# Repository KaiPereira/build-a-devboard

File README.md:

# Let's Design an RP2040 Devboard!

Today, we're going to be designing our own dev board, using one of the most popular and beginner friendly SoC's, the RP2040. This guide doesn't serve as just a tutorial, but also as an opportunity to learn what everything on the PCB fundamentally does, and what every single component on your PCB is actually for!

All the source files for this tutorial can be [found here](https://github.com/KaiPereira/build-a-devboard), so if you need any help, feel free to resort to the repository!

Now let's start off with the basic question, what's an SoC! An SoC or system on chip, basically has all the basic components like SRAM, processors, USB controllers, and other peripherals you'll break out onto your board. The RP2040 is a good SoC to start with, because the datasheets are simple, it's low-cost, has good on-chip memory and is really flexible with plenty of IO's.

Now let's get right into it, we'll be using KiCad for this tutorial, and I would suggest completing the hackpad tutorial and maybe a keyboard before trying to make your own devboard, not because you won't be able to make it, but you'll understand how it works a bit better.

So create a new KiCad project by going:
`File -> new project, and choosing your name/folder for the project`

After that, double click your schematic to start working on your PCB. PCB's essentially have 2 main parts, the schematic, and the actual PCB. 

The schematic is basically a wiring diagram, that shows how everything will connect, but isn't like exactly where the components are placed or how thick your traces are, it's solely to show how everything is wired, not where.

*This is how are schematic will look when done the tutorial*

The PCB editor is where you'll place down all your components and route everything for when you get it actually manufactured.

## Starting the schematic

So enter in your schematic, and then tap "a", this will open up the symbol library, which is the place where you can find component blocks that you'll wire together to form the schematic for your project. Search for the RP2040, and just place it down in the center of your schematic.

You'll notice the symbol and actual component are 2 different things if you look at the first screenshot. The symbol just tells you all the pins on the component, and how they'll be wired to what. The actual component has the physical pads where traces will actually connect to on your PCB!

Our entire schematic will consist of 5 main elements: power, flash storage, the crystal oscillator, I/O (input/outputs), and your SoC, the RP2040! The Raspberry Pi datasheet explains how all of this will pretty much be wired, and I'm kind of just here to explain exactly how it all works too.

So first let's talk about power and some schematic good practices!

You'll notice that the RP2040 has capacitors, these are called decoupling capacitors. These capacitors are used for 2 main things, filtering out power supply noise and giving a local power supply if components need it at short notice. You can think of it like a stream of water, without the capacitors it can be jittery and unpredictable, but with the capacitors, the stream smooths out, making your PCB function more reliable.

You usually want to put one 0.1uF (or 100nF, the F stands for Farads) decoupling capacitor per power pin, but it's fine to deviate a bit from that, but that's the most optimal way of doing it and what we're going to do.

We're also going to put a 1uF decoupling capacitor on each power line. You'll notice that the RP2040 has a +1V1 (1.1V) and a +3V3 (3.3V) line, we want to put a 1uF decoupling capacitor per line, to act as a larger reservoir and to smoothen out *larger* ripples that could occur. With the RP2040, these 1uF capacitors are mostly to help provide a stable 1.1V supply. With this combination, we'll filter out nearly all the noise and have a smooth functioning PCB.

So go back into your schematic and then tap on the "Draw Wires" icon to connect the VREF_VOUT and DVDD, and then separately connect the IO_VDD, USB_VDD, ADC_AVDD and VREG_IN, because these pins have different voltages.

**Now before we go further, remember that all power labels face UPWARDS, and all ground labels face DOWNWARDS, this isn't necessary for the schematic to work, but it's good schematic practices that you should always follow**

Then tap "p" to open up the POWER symbol library (you can also tap a, but searching in p will be faster because there's less symbols), and search for "1V1" and "3V3" and place the 1.1V on the VREG_VOUT and DVDD, and 3.3V on the IOVDD and those other pins.

**Now schematic good practices is to always put at least a small wire between symbols like this for clarity.** 

Now that we have our power symbols in, we're going to add the decoupling. You could technically wire them like the screenshot I showed before, but I prefer to separate them because you use less wire which I find looks cleaner, but it's up to personal preference, and readability.

You'll also notice that the symbol contains less pins than the symbol the RP2040 datasheet has, this is because symbols in KiCad tend to not repeat the same pins, so they just merge like all the same VDD pins into one.

But using the RP2040 datasheet as reference, we know that there's 8 IO VDD pins, so eight 0.1uF decoupling, and one 1uF cap because we're wiring the entire 3.3V line and need to smooth out the larger ripples. So let's just place all those in!

Again type "a" and search for "c" (the shorthand for capacitor). Make sure to double tap the capacitors to add a value, and make eight of them 0.1uF, and one of them 1uF.

These are the decoupling capacitors for the 3.3V line, now we need to do the caps for the 1.1V line. There's 2 VDD pins, so two, 0.1uF caps, and we need one for the line too, so a 1uF cap aswell:

Now we have all of our power decoupling. We also need to connect GND to the SoC, this is pretty self-explanatory, but it allows power to actually flow properly in our PCB.

## Working on USB-C

We have our power decoupling, but we don't actually have a power source yet or a way to program our devboard yet, so let's do that now. I'm going to be using USB-C because it's standard and fast!

So tap "a", type in whatever receptacle you want, and add it in. Make sure you pick "receptacle" and not plug because a plug would plug into your laptop instead of having a cable plug into it.

Now let's explain each of these pins:
- SHIELD/GND will both go to ground, shield is conductive material wrapped around the data pins on the receptacle, and this just improves EMI by grounding it.
- D+/D- are the data pins, these transfer data to/from the USB-C receptacle. You'll want to connect the D-'s and D+'s together so that they both transfer data.
- CC1 and CC2 basically tell the receptacle to allow power to go through to power the board. These by standard (the datasheet tells you) are pulled down (go to GND) through 5.1K resistors.
- VBUS is the 5V input, this will need to be stepped down to 3.3V to power our MCU (microcontroller)

Now that we know what everything does, let's wire it up. Shield/GND go to GND:

D+ and D- are attached to their relative pair, and then will go into the MCU, but for now, we'll just have a global label going out of them. Global labels are basically like little teleporters, that allow you to say that something is wiring, without manually putting a wire between them. 

Technically global labels are meant to be used between different schematic sheets and net labels would be the correct thing to use here, but I find global labels are cleaner if you only have one schematic for your PCB.

To do this, tap global label in the right hand toolbar, type in the name for your label (USB_D+ and USB_D-), and add them to the pins:

Next, pulldown the CC pins through a 5.1K resistor to GND to enable power to go through the USB-C receptacle. Open up the symbol library, and then type "r" the shorthand for resistors, and then place it down and edit the value to be 5.1K:

**Remember to follow proper schematic good practices, and to have clearly visible values, and labels for your components**. Feel free to edit the text of stuff to make your schematic cleaner, just don't make stuff *too* small.

Now we just need to wire in the input voltage, but the thing is, the voltage of USB-C is 5V, while the voltage that the RP2040 uses as input, needs to be 3.3V so you don't cook it. To achieve this, we'll use what's called an LDO, or a Low-Dropout Regulator to take the voltage down.

Specifically, we'll be using the **NCP1117**, a classic and reliable *fixed* voltage regulator **(I actually switch this regulator out later for the MCP1700, 3.3V, because it's really big on our PCB)**. A fixed voltage regulator is handy here, because we only need to go down to 3.3V instead of like 1.5V per say or something random, and it uses less components. We'll also be using the SOT-223 footprint (or package is the common term) because it's small and we don't really have any thermal issues with a devboard.

So add in the **NCP1117-3.3_SOT223** symbol, wire GND and attach VBUS to the VI (voltage input) of the LDO.

Remember to always keep your schematic clean and feel free to use up quite a bit of space. Now like the decoupling capacitors on our RP2040, we need capacitors on the LDO. But we don't need fine decoupling capacitors for precise input lines into an MCU, and instead we need **bulk** capacitors, to handle the large voltage ripples when moving a voltage down.

So we need to place two, 10uF capacitors on each side of the LDO, for input/output, so add them into your schematic:

Next, we want to add our power labels to the LDO, we'll put a VBUS label **before** the LDO/Bulk cap, and a +3V3 label to the VO (voltage out) of the LDO. We might use 5V to power some other devices so we'll want to provide a power line for that too:

Now to finish off the USB-C wiring, we need to make sure the MCU receives the data lines. It's standard to have these going through 27 ohm resistors into the MCU to prevent distortions of the signals at high speeds, these are called *termination resistors*.

So wire the USB D+ and D- pairs into the MCU USB_DP and USB_DM (the P is for + and the M is for -) through 27 ohm resistors:

Now USB D+ and D- are actually what's called "bidirectional", this means that they work both ways. You don't actually need to specify this, but good schematic practices is to make sure your global labels reflect that. Currently they're just set as "inputs" because the triangle is facing inwards, so double click on all the D+ and D- labels and set them to bidirectional:

## The crystal oscillator

Now to make our USB and other peripherals actually work properly, we need to have what's called a crystal oscillator. This is a little piezoelectric quartz crystal that vibrates very precisely, and then it's amplified and fed into the MCU to act as a clock signal that controls the digital peripherals.

For example, you definitely want a crystal oscillator if you're using USB-C, because the data needs to come in at specific times, so it makes sure no data is incorrectly received. Because the clock is such a precise component, you want to wire it really carefully. That means it should be as close to the MCU as possible on the PCB (schematic doesn't matter, it's just a reference), and it needs really small capacitors, to smooth out the signals.

First add the global labels to the MCU XIN and XOUT, just called their relative name. XOUT is the output from the crystal so an input to the MCU, and XIN is an output from the MCU to help the crystal oscillate properly:

Remember to accurately represent your global label direction, but just keep in mind it doesn't actually change your schematic, it's only for whoever is reading it!

Based off the RP2040 datasheet, we're going to be using a 12 MHz crystal with two, 15pF (I switch these later to 33pF because we use a different crystal than the Pi Pico) decoupling capacitors. **Make sure to use the crystal footprint with 4 pins and 1 and 3, as the input/output pins so pay attention to the symbol I use**:

Pins 2, and 4 just go to GND, pins 1 and 3 need a 15pF cap in series, and XOUT will have a 1K resistor. This resistor is called a damping resistor and it prevents the crystal from being damaged and ensures good signal integrity:

Remember all your schematic good practices and make sure everything looks clean.

We haven't actually seen these types of caps yet, these are called external load capacitors, and they're placed in series with the crystal I/O's, these basically just ensure that the crystal resonates at it's proper frequency, I'd suggest researching a bit more if you're interested!

## Flash storage

Now lot's of SoC's include flash storage, but the RP2040 actually doesn't, so we need to add on our own flash storage! You can think of flash storage as like a faster version of an HDD, with less power consumption, more reliability but is usually a bit more expensive.

Sadly, the RP2040 only supports up to 16mb of memory, so we'll just use a quad SPI flash memory IC (integrated circuit, those little chips on a board) like the **W25Q128JVS** used in the datasheet.

Now before we actually add it to our schematic, let's talk about what SPI is. If you continue to build PCB's, you'll see this communication interface very often, it's basically just a standardized way of transferring data. The signal comes out of the master, and then goes into slave devices. The master is our MCU in this case, and the slave, is our flash memory.

It has 4 major pins you need to understand:
- MOSI - Master output, slave input
- MISO - Master input, slave output
- SCLK - Clock signal (remember that oscillator we added to our board, this will basically do that for other devices)
- SS/CS - Slave select, let's you choose what device you're communicating with

So you usually need to have all 4 of those, and then you can add SS pins as you wish if you want to communicate with more and more devices.

**But we're actually using quad SPI in this case.** 

Quad SPI uses the same CLK and CS pin, but has 4 IO pins, so it can transfer data, 4x as fast as SPI, which is ideal for flash memory, but it does take up more pins, so that's why it's not always used. 

Now you can't just attach SPI to any GPIO, you have to use what's called a hardware controller, which you can imagine, is like a little block on the RP2040 SoC that is specifically meant for SPI. There are 2 SPI controllers on the RP2040, so we're going to use them for our flash memory. You can also technically do SPI via software, but it just makes way more sense to use the actual controller provided.

So add a global label to the QSPI pins with their relative name, IO's are bidirectional, and CLK and CS/SS are inputs to the slave (the flash memory) or outputs from the MCU.

Next, add in our flash memory IC (chip), **W25Q128JVS**, and wire up all the QSPI pins, and put GND to GND, and VCC to 3.3V:

Next, we need to add our 100nF/0.1uF decoupling capacitor to our VCC line to filter high-frequency noise. And then, we're going to add a button to the CS line, so that we can enter what's called BOOTSEL mode.

Based off of the RP2040 datasheet, if the QSPI SS pin, see's a 0 or GND when it's booting up, it'll go into BOOTSEL, where it will appear as a USB device on our computer so that we can copy code onto it to set it up.

Now there's 2 resistors you're probably wondering about here, the pullup to 3.3V, and the one in series with the button.

The pullup to 3.3V is important, because usually the QSPI pin will show up as 3.3V to the flash memory, but during bootup, you can't guarantee that it will, because the pin isn't active, so you might have some weird thing that happens with your board. The 10K resistor is just standard that the RP2040 datasheet wants us to use (and is also pretty commonly used to filter noise and stuff).

The 1K resistor in series limits the amount of current that can flow in this part of the circuit to prevent damage to the CS pin.

And just like that, we have our button and decoupling in, and our flash memory is completed!

## Breaking out I/O Headers

Now we have all the components for our board to actually work, so we just need to breakout all the GPIO's on the RP2040, onto header pins so that we can use them in our circuit and whatnot!

But before we do this, let's just make sure we attach TESTEN to GND on the RP2040, this pin is just meant for factories to make sure that the RP2040 SoC actually works before sending them out.

Next, we'll label all the other pins we haven't broken out (all the GPIO's, SWCLK and SWD), with their relative name on the RP2040. These are all bidirectional pins except the SWCLK pin, which is a clock output from the SoC:

*I actually labelled mine the wrong direction for the rest of this tutorial, but it's purely cosmetic and won't actually impact my PCB, this is how it should actually look, don't mind the GPIO labels, I took this screenshot after being done the PCB:*

Next, we're going to add the actual header pin symbols into our schematic. You can technically do this whoever you want, but I'm going to adhere to the raspberry Pi Pico pinout:

So add in a two, 1x20 header pin symbols, and one 1x3 header pin symbol, I just used generic symbols, but you could use pin header symbols if you want, it's just up to preference:

Usually you don't want to make your symbol layout look exactly like your PCB, but I think it makes it more obvious so that we don't mess up our pinout!

Next, we'll just add in all the pins, and we'll just leave out the ones we don't know yet like VSYS, 3V3_EN and ADC_VREF, I'll explain those after:

Now the Pi Pico can actually be powered by a battery, but we're not implementing a battery (if you want to, check out the Pi Pico datasheet), so there's a diode on the VBUS power line, so they have a VSYS line after the diode and a VBUS line before it, but because we don't need a diode, we don't need VSYS.

We also don't need 3V3_EN, and then ADC_VREF is kind of just another thing to give a reference voltage to ADC, but it isn't really necessary, and we're just making a simple devboard so we won't use it.

Because we have these free pins, and also some GPIO's still left, let's just fill these pins with some GPIO's. I'm going to move the ADC pins up, and then fill the other pins with GPIO's. I also want to use GPIO29 which is an ADC pin and replace GPIO25 with that just so we get the added ADC pin:

Because of this, you'll want to just no-connect GPIO25 on the MCU, just to tell KiCad and others that we're not using that pin:

If you want to add battery support, you can do so yourself, but I'm keeping to a minimum framework. And just like that, we have all of our header pins in!
## Finishing up the schematic

Now that we have our I/O headers in, we're actually finished with all the symbols in our schematic, this is how your schematic should look:

Now to organize our schematic, even more, let's separate our design into different blocks using the text boxes in the schematic editor. When doing this, you usually want to place your component blocks by flow of your PCB. So if you could image, power flows in through the USB, so we'll put that in the corner, the MCU should be center because it's the fundamental of the PCB, and then the other stuff can just be organized around:

You don't have to do this, but I feel like it keeps everything nice and clean!

Next, run ERC to just make sure you don't have any unconnected or weird stuff happening in your schematic. The only error you might get is **Input Power pin not driven by any Output Power pins**. You can just ignore this error, it's basically just the fact that we're labelling our power as bidirectional, and with no input/output, but we know that the MCU takes in 3.3V and that the USB-C outputs 3.3V, so we're totally fine to ignore it.

## Footprint time!

Now that we've finished out schematic, we need to start working on the actual PCB. The first thing you need to do for the actual PCB, is to add in all the footprints for your components.

A footprint on a PCB basically just defines it's pads, outline, etc, that your component needs in order to be solder able on a PCB. So just tap on the **assign footprints** tab in the top toolbar to open up the footprints tab:

Now before we add in our footprints, let's talk about standard imperial sizes of SMD components, and SMD vs THT components.

So if you don't know, there's SMD components, which are surface mount, which means that the components are attached to the surface of the PCB like caps, and then there's THT components, which are soldered *through* the board, these are things like the headers.

For SMD footprints, you'll want to understand what the imperial sizes are:
- 0402 are the smallest footprint we'll have on our PCB, these are tiny footprints and anything smaller than this becomes too small to easily solder, these are good for low current applications, and are fine for our fine signal decoupling.
- 0603 footprints are a bit larger than 0402, and are better for slightly higher current and will maintain better physical stability for the larger decoupling needed for 10uF caps and such.
- 0805 footprints are pretty large and are really just needed in higher current applications, we won't be using any of these because we don't have any crazy large caps/components

So all of our 0.1uF/1uF/resistors will be 0402, and then the 10uF caps will be 0603, so just filter in the search bar for 0402/0603, and choose the resistor/capacitor footprint for the relative component:

Now these other components need to usually be found on LCSC and then you go into the datasheet to find the footprint, and then add it in, but I'm decently experienced and know what footprints to use already, so you can just copy what ones I'm using or [find your own](https://jlcpcb.com/parts) if you want and add them in:

These are my thought process behind the other components, JLCPCB has what's called basic and extended parts, and extended parts cost $3 each to add to a PCB because they have to be loaded into the assembly machines, this will be important here:
- **USB_C_Receptacle_HRO_TYPE-C-31-M-12**: JLCPCB doesn't have any basic part USB-C receptacles, so I just chose this one I kind of like from a previous board. [PART](https://jlcpcb.com/partdetail/Korean_HropartsElec-TYPE_C_31_M12/C165948)
- **PinHeader_1x20_P2.54mm_Vertical**: This is just the proper size header pins we need, they should be through hole/THT to be stronger instead of SMD, I mean if you wanted to, it could be SMD though. The part is just pin headers I'll buy separately
- **SW_Push_SPST_NO_Alps_SKRK**: This is a small SMD size button footprint found in the JLCPCB *basic* library, so it doesn't cost anything extra and is pretty compact. This isn't actually the EXACT footprint, but it's close by like .1mm, and I found it by just scrolling through footprints with some filters. [PART](https://jlcpcb.com/partdetail/XUNPU-TS_1088AR02016/C720477)
- **Crystal_SMD_3225-4Pin_3.2x2.5mm**: I found this crystal on JLCPCB basic parts, and looked at the datasheet to find the footprint. You really have to make sure your crystal footprint pinout is proper because lots of people accidentally use the wrong footprint or symbol. [PART](https://jlcpcb.com/partdetail/YXC_CrystalOscillators-X322512MSB4SI/C9002)

Now we actually need to modify our crystal schematic a bit because of the part we chose on JLCPCB has a load capacitance is slightly different, so we actually need 33pF caps. You can just search up the math if you want to learn how to do this:

And just like that, our schematic and footprint selection is finished, so we can actually get to the real fun stuff.. the PCB!

## Let's design a PCB

Now that all that stuffs done, tap the switch to PCB editor button on the far right of the top toolbar!

This will bring you into a new editor you haven't seen yet, this is where we'll actually place down the components on our PCB, and route everything.

So in the top toolbar, tap the **update PCB from schematic or F8**, and then tap the **update PCB** button that shows up, to bring in all the components into your PCB, and just put them all in the top left corner of your PCB:

You might get some warnings which can be ignored usually (I just got some pin warnings which are fine), but there shouldn't be any errors.

Now you'll see our actual components on the PCB, our USB-C, the RP2040, the button, crystal, LDO, flash, headers and our caps/resistors!

## PCB Layout

Now before we actually lay out all of our components, we need to define our PCB outline, holes, etc. So using the datasheet as a reference, we'll place down everything accordingly. Start with the board outline, and then do holes and stuff.

To add in a board outline, **tap on the Edge.Cuts layer** and then tap on **Draw Rectangles**, and then just put whatever size rectangle you want. After that, we'll add in the proper size from the datasheet, which is 21x51mm, so tap on the rectangle, then tap **"e"** and use the **By Center and Size** tab to do this:

Next, we'll align the header pins onto our PCB by using the position tool. So right click on one of the header pins, go **Positioning Tools -> Position Relative To**, and then go **Select Point** and tap one of the top corners of the board outline. And then using the datasheet, align the X to **1.61/-1.61** based off of the side, and the Y to **1.37**:

(I actually swapped my pin headers here which I fix later, but just put J2 as the first header, and J3 as the second one, so it's easier to route)

Next, we need to put our bottom header in, these are aligned to Y **-1.61** and the X should be centered so **7.96** (10.5 is the center, minus 2.54 the pin spacing), and use the bottom left/right as reference (make sure it's flipped horizontally when aligning):

Next, I'm going to put in the RP2040 dead center, but with the Y slightly farther down, because there's more components above the Pico than below, so I want a bit more space for signals, I'm going to put it down an extra 4mm, but you can do how much you want. 

Then, I'm going to center the USB-C, down a bit to the top of the devboard:

Now looking at the flash memory and LDO IC, they're really big, so let's use different components for them:

I'm going to switch to the MCP1700 LDO, which is smaller, but does handle less current (250ma), so if you plan on drawing more current, you might want to just keep the current LDO. So just replace the NCP1700 with the **MCP1700x-330xxTT**, which is the 3.3V MCP1700:

And then, we're going to change the flash memory to what the Pi Pico uses and has a slightly smaller package, which is the **W25Q16JVZPIQ TR** and uses the **Package_SON:Winbond_USON-8-1EP_3x2mm_P0.5mm_EP0.2x1.6mm** footprint, so switch the footprint to that new one!

Now your footprints should be much better:

Anyways next, we're going to organize our parts onto the PCB (I also fixed my header pins and MCU orientation in this step). The LDO is going to go really close to the USB-C VBUS, and the flash storage will go close to the RP2040's QSPI pins, just so we have an efficient layout:

I use exact positioning when doing things like this, but you can just place them on if you want, I just like everything to be nicely symmetrical.

Next, I'm going to put the crystal on. The crystal should be very close to the RP2040 XIN/XOUT pins because it's a very precise signal, and the load capacitors should be RIGHT next to the pins too so the signals don't get messed up. You can then just put the resistor right by the XOUT pin of the RP2040 to have a nice and efficient layout:

Now I'm going to put all the decoupling capacitors on my board. **Decoupling capacitors should be as close as possible to the pins they're decoupling**, the larger the cap is, the farther it can be, but try to keep them close to their pins.

Also feel free to mess with layout a bit during this step just so everything fits in efficiently! Try to use whatever capacitor you used in your schematic for organization purposes.

First I usually group all the caps that go together, and then I usually either start with the SoC caps, or components caps, I'm going to start with the components caps:

**Remember, caps go close to whatever they're decoupling**. Now all the RP2040 caps are grouped together, and this is because it's just a general rule to have one cap per VDD pin, and then the larger cap/bulk cap near the largest group of them:

This is the layout I decided on, some of my thought process for this layout was:
- Leave enough space to route the USB differential pair
- Be able to route QSPI without via's for fast signals
- Leave enough space by the crystal to be able to route those traces

And I'll still definitely actively update it while I route my traces, but this is a good starting point.

Now all that's left to add in, is our resistors, but I'm going to actually put these to the side, and start routing a couple things! This is because it's going to be easier to place components not in the way of where traces are going to go.

**Not before we start routing, remember a couple key things about routing:**
- Never have a trace at a 90 degree angle, these mess with your signals, and also sometimes get manufactured weirdly
- Think about what you're going to route next, so that you don't route where that trace needs to go
- Know what you're routing, things like decoupling caps need to have short, small traces, etc.
- Never put via's on pads, this makes it hard to solder them, and makes the component unstable
- Try to route front signals vertically, and back signals horizontally, this isn't a fixed rule, but just try to do it in most spots to have efficient routing
- Don't be afraid to move your components a bunch while routing, a lot of intuition is required for efficient routing
- You might hear me use the term "ratlines", these are the blue lines on the PCB, I actually have mine set as curved because of personal preference, but yours will probably be straight

So, the first thing I'm going to route is my flash memory, I'm going to move the capacitors away temporarily while I do this and then add them back on later. So tap on the **route single track** in the right hand toolbar, and then route all the signals like so:

I usually start my route from the RP2040, and then put it into the component just because I find it's easier. I always start with routing my higher speed signals, and then do the lower ones.

Next, I'm going to route the USB-C data lines. Now these lines are actually special on our PCB, these need to be routed as differential pairs, basically perfectly even traces, next to each other. This is because they're carrying high speed data, so the traces need to be the same length so that data arrives at the same time.

The termination resistors for these data lines also need to be right by the RP2040 pins to smooth the signals. I'd suggest placing these perfectly evenly apart, centered on the pins so it's easy to route our differential pairs:

Now to route a differential pair. First wire the USB D+'s/D-'s together:

Then, **hold the route tracks button**, and go over to the symbol with 2 traces on it, or just **tap 6**. Then, go over to your USB-C, and tap on one of the D+/D- pins to start the trace, and route it down to your resistors. If the traces won't go into your resistors pads, that means that your resistors aren't evenly positioned, you can just the relative positioning tool to do this. 

And then you can just route the resistors nets into the RP2040 nets (Make sure they're centered so the traces are the same length, you could technically do this as a differential pair if you change your schematic slightly, but it's fine if you just position properly):

I added left a space inside of the USB traces for the decoupling capacitors to go.

Now we need to make sure all these traces are the same sizes, you can check the resistor traces by using the **Tune length of a single track** tool on the right toolbar, they should be the same length if you did it right:

And then, your USB-C lines, are probably not the same length, so we need to fix that. You can do that by going to **route -> Tune skew of a differential pair** in the top menu, and then selecting the trace with a *negative* skew, and just tapping it, and then tapping **ok**, and then just drag to make it slightly longer:

This makes all of our traces the exact same size, so that we have proper data flow! 

Now we just need to wire the extra pair of D+/D-'s on the USB-C to the route that we already have. Just wire these directly 

Now that we have our fast signals on the PCB, the other signals are fine to go through via's, so we can put in our decoupling caps now:

**Leave all of the ground pins for last, I'll explain this soon**

Now my routing of course isn't perfect, but I did manage to get it pretty nice and tight. You'll notice some blue on the PCB, and that's me routing on the other layer. You can change layers by tapping the other layer on the right layers view, or by **tapping "v"**. But for SMD components, you'll need what's called a **"via"** in order to get to the other layer, which is essentially just a hole that allows traces to transfer to another layer of a board. Feel free to use the backside for routing if you don't have any space!

Anyways, next I'm going to route the crystal, the USB-C pull downs, and button pull ups, and then I'm going to leave the button/button resistor for very last because there's no specific spot that needs to be:

Now, we're going to route power to our board, I'm distributing power to the main cluster of VDD pins, and then once I'm finished routing the other signals, I'm going to route it to the other pins, just so power is even about my board:

Now, wire every single header pin on the board, try to keep organized when doing this, and save via's/the other layer for when you have like absolutely no space left:

And with a bit of finesse, all of our routing is pretty much done, we just have all of our ground signals left. Now you're probably wondering why we didn't route those. Well instead of using wires to do those, we can use what's called a ground fill.

This is basically like a giant pool of just ground on our PCB that connects all of our grounds together. We do this because it helps with signal integrity, and because there's always going to be a lot of ground signals on a PCB so it simplifies stuff. It also helps with thermal regulation!

So on the right toolbar, tap **Draw Filled Zone**, and select both layers, with GND as the net, and select *Thermal reliefs* as the Pad connections. Basically, with a ground fill, soldering can become harder because the fill dissipates heat, so doing thermal reliefs puts like less ground area to the hole so it's easier to solder stuff on!

Then, select the entire PCB with your ground fill, and then **tap "B"** to fill it:

Now you'll notice that all your ground ratlines disappear. Their might be a couple that are still there though, this is because the pads are isolated, so you might need to put a via from the pad onto the ground fill. You also might need to adjust like some of the header pins signals and such to make it work!

I'd also suggest adding via's to all the isolated islands of ground for signal integrity, but this is just good practice, and also putting extra near the SoC and stuff that get's hot like the LDO:

Next, we'll need to add in our button that we haven't put in yet. Just find a free spot on your PCB for it, I'm going to put mine near the flash memory though because it's got some space and it's a close connection:

And then, if you just have any ratlines still on the PCB, just connect them up, and you'll be on the final step of designing our PCB:

Now you probably think, we'll we're done the PCB, what else could there be, well there's actually a couple more things we need to do. The first thing is running DRC to make sure there's no problems with our PCB. **So go to the top toolbar, and run DRC**:

My PCB has 16 errors, yours might have more, but all of these need to be properly resolved. The first things I'm going to look at is my unconnected items. These just tell me what I forgot to route, you can just tap on them to see where they are, just make sure you get all those routed before continuing.

Most of these are problems with the ground pour, so I'm actually going to modify the ground fill to fix a lot of these errors, I'm changing the thermal relief gap and clearance to 0.3mm instead of 0.5mm which just makes it so the traces and pads can be closer to the fill:

You'll probably also have a bunch of thermal relief errors. These require some finesse to fix, but essentially you just need to have like a thick enough ground on each component. And you can solve this by adding via's, traces, and a bunch of other stuff like editing the fill. So you'll need to research a bit and try different things to fix these. And not all of them are even too crucial, but I'd suggest fixing them all.

The rest of the DRC errors you'll have to figure out, but here's how mine looks with no errors left:

## **Congrats on finishing your devboard 🥳**

Now you've finished making your actual PCB, if you want to get an idea of how it'll look when manufactured, you can tap the **3D Viewer** in the top toolbar:

The headers will be facing the other way and you can't see the USB-C because it doesn't have a 3D model, but this is how your PCB will look. If you want the header pins to actually be right, you might be able to flip them on your PCB, or double tap the footprint and directly change it! Pretty cool huh, but you know what would make it even cooler... **Art!**

## Working on silkscreen

Now before we get all excited, let's polish up our PCB a little bit! We're going to do this by modifying what's called the silkscreen, this is all the white stuff you see on the PCB, it's purely decoration and used to show where components should go when soldering, and also to label stuff, and you can make art with it.

But before we get to make the art, let's move all the labels on our PCB to look nice and organized! Now the capacitors and stuff aren't too useful to us, so we can delete those silkscreen labels like "C#" or "R#", and just leave the important ones for the connect, the pi, etc.

I'd suggest hiding some layers to make it easier to see, so delete all the stuff we don't want, and organize the stuff we do want (You can also hide the fab layer for now, but there's no need to delete that stuff, it won't be on your PCB):

This is how mine looks when done:

Now, let's add our own art! Try out the KiCad image converter, and also add some text and stuff to your PCB. I personally like to add things like my website, github handle, favorite animals, anime, whatever you want really.

I personally use excalidraw to draw my art but you can do whatever:

**And that's our PCB finished!** Run DRC one last time to make sure you have *no errors*, and then continue on to the final step, which is getting this thing manufactured!

## Fabrication time!

Now that we've finished our PCB, let's get it fabricated. Save your PCB, and then go to:
```
File -> Fabrication Outputs
```

and then export every single thing there, if you want my gerber settings, here they are:

**Now you can also use the KiCad [fabrication toolkit](https://github.com/bennymeg/Fabrication-Toolkit) to do this all for you if you're having problems, but I like to teach the whole process**

And before you turn all these files into a zip, you'll want to modify the CPL file, because JLCPCB expects the CPL file headers to be called something else, so add it into google sheets. This file will be called something like **"your-project-top-pos.csv"**, we're doing one sided assembly so you can delete the bottom file. Anyways change the headers from:
- Ref -> **Designator**
- PosX -> **Mid X**
- PosY -> **Mid Y**
- Rot -> **Rotation**
- Side -> **Layer**

Next, you need to replace the headers on your BOM file, this is just changing **Designation -> Comment**

Once you've renamed those headers exactly, export is as a **.csv** and replace your old CPL/BOM file with this one. And then take all of the files you exported, and compress them into a zip folder, called "PRODUCTION" or whatever you want really:

And now I usually make another folder called production in my root, and put this zip file inside of there:

Now head on over to JLCPCB and drag that zip folder into the quote section. You should see your PCB show up, and the only thing you're going to add onto your order is PCBA, this just makes sure that JLCPCB doesn't just give you the raw PCB, but also assembles it:

*Now you don't actually need to use PCBA, if you want to save some money, you can just buy the components on LCSC or the JLCPCB parts manager (which will probably be cheaper), but you'll need to have all the tools to assemble SMD, but I'm going to include an SMD soldering part to this tutorial too if you want to do that*

Now tap next, and then add your BOM, and the CPL CSV you just created. If you have any errors when uploading this, check the internet, double check you modified the CPL/BOM properly, and worst case, tap the chat button on the website and ask the JLCPCB help desk.

If you did everything properly though, you should be presented with the JLCPCB BOM page:

Now we need to assign the parts that JLCPCB couldn't automatically find and the ones it got wrong. In most cases this is just a quick search and then tapping the first result, but make sure what you select is exactly what you actually want. The 27 ohm termination resistor is also probably going to be wrong, so you'll want to re-assigned this to a proper 27 ohm resistor.

**Make sure not to select the pin headers for PCBA, these are easy to solder our self and aren't worth it to pay for, just buy these separately.**

**Also make sure you're using as many basic parts as possible, filter for these so that your PCB is cheaper when selecting parts, but sometimes parts aren't available as basic**

This is what my final BOM looks like, feel free to copy mine (it'll be in my GitHub repository under /PRODUCTION/files too):

Now continue on, and don't place the header pins (it'll prompt you), and then you'll see your assembled board show up:

But there's a couple components that aren't properly assembled on our boards so we need to move them manually!

You'll need to move:
- The USB-C to fit within the holes nicely
- The LDO just needs to be turned a bit
- The flash memory needs to be rotated right so that the dot aligns with the triangle

And then everything else you should just double check, but it should be fine:

Now, tap next, and **congratulations, you're done your PCB!!!!**

Congratulations on making your first PCB!! I know that this seemed pretty hard and complicated, but it gets so much easier with practice, so keep on making cool stuff!

Now try to challenge yourself in your next endeavor, and don't just make another devboard, try your hand at a motherboard, or a power controller, just something that challenges you and helps you learn!

Feel free to also modify this board you've created to include an LED matrix, motor drivers, literally whatever your heart desires.

I hope you learned alot, if you want to checkout some of the other stuff I've created, check out my projects on [GitHub](https://github.com/KaiPereira) or my personal website https://kaipereira.com/! Don't forget to post your finished projects in #ship and ping me (@KaiPereira) too!

Now if you want to stick around, we're going to go through assembling your PCB, if you didn't want to get JLC to do PCBA!

## Hand-soldering your Devboard!

Now if you've decided to take the VERY FUN ROUTE of hand soldering your devboard, I'll continue with a small tutorial on how to do so!

Now hand soldering is mildly difficult, and takes quite a bit of time, but you'll learn invaluable skills lots of other people don't learn, and also earn a lot of tickets while you're at it :D

So the first step is buying all your components for hand soldering! Everything can just be bought on LCSC, and I'd suggest buying a couple extra components of each thing, just in case you accidentally mess up/break components!

You'll also want to have a couple other key components:
- Flux paste (not solder paste), this helps the solder bond to the pads of your board, helping to fix mistakes and is crucial. This will come in a little syringe container, and looks white/yellow depending on where you get it from (solder paste, which you don't want usually look gray!
- Fine tip soldering iron, this makes soldering in really tight spots so much easier, most tips are usually fine enough, but you just don't want like a super wide one.
- Solder, usually smaller solder is usually more convenient, but it's honestly fine to use larger
- Fine tip tweezers, I honestly wish mine were finer, but I'd suggest trying to find the smallest fine tip tweezers in your house that aren't ribbed/textured at the end
- Brass sponge, for cleaning your tip, you just dip your iron into this every once in a while to get the excess solder off!
- Silicon mat, this isn't needed, but I would HIGHLY suggest, so that your soldering iron doesn't fall off and burn you, and so you have a nice grippy surface to hold your PCB on
- Decently ventilated area, honestly I find this is less for saving you from the unhealthy fumes and more to get the smoke out of your eyes so you actually see what you're doing!
- Isopropyl alcohol and Q-Tips, these are to clean up the flux on your board after soldering, it's just once you're done, so you don't really have to have it on hand before starting!

This is what my setup looks like with all of these things:

*Pretty sweet right :D*

Now you're ready to get soldering!

When you're soldering a small board like this, and most PCB's for that matter, you'll want to start with your smallest components first and then work your way up. In our case, we have quite a few 0402 components, which are going to be SO MUCH FUN to solder.

Lots of people don't spend time to actually learn how to properly solder these components and just go at it, but I'll try my best to describe it and you'll also want to [watch this video](https://www.youtube.com/watch?v=EW9Y8rDm4kE) in it's entirety!

So basically:
- Apply your flux around/in the pads of the footprint of the components you're going to solder
- Apply solder to one pad of the footprint
- Place your component onto the footprint
- Apply heat on the pad with solder while it's touching your component
- Take your tweezers off the component
- Apply heat to the other pad, and solder it to the component
- Apply more solder to the pad you first soldered to create a stronger connection

And then you're done! I sometimes add some more flux and then clean up my joints, but it's up to you if you want to do so! This will be hard when you first start off, but it get's much easier with practice, and also better tools help a lot!

Now you want to pay close attention to your joints, to make sure that your solder is actually joined with the component! I find being in a WELL lit room helps a lot to see everything, and a microscope can be very handy!

If your component didn't form a joint with one of it's pads, you might need to get the component closer to the pad or apply flux, or apply more solder!

If you ever bridge 2 pads with solder, apply flux and they should go back to their relevant pads, it's MAGICAL....

Tutorials help a LOT here where words sometimes can't explain all, so take your time, and do it right.

I started by soldering my 0.1uF caps, because there's quite a few of them, but you could really start with whatever 0402 component you want, and then work your way up to 0603, then 0805, and then small components, then large components!

Here's my very first passive soldered onto my board:

Yes, it's SMALL, and takes lots of time. If you're currently working on this, shoot me a DM on slack **@KaiPereira**, I'd love to see how you're doing!

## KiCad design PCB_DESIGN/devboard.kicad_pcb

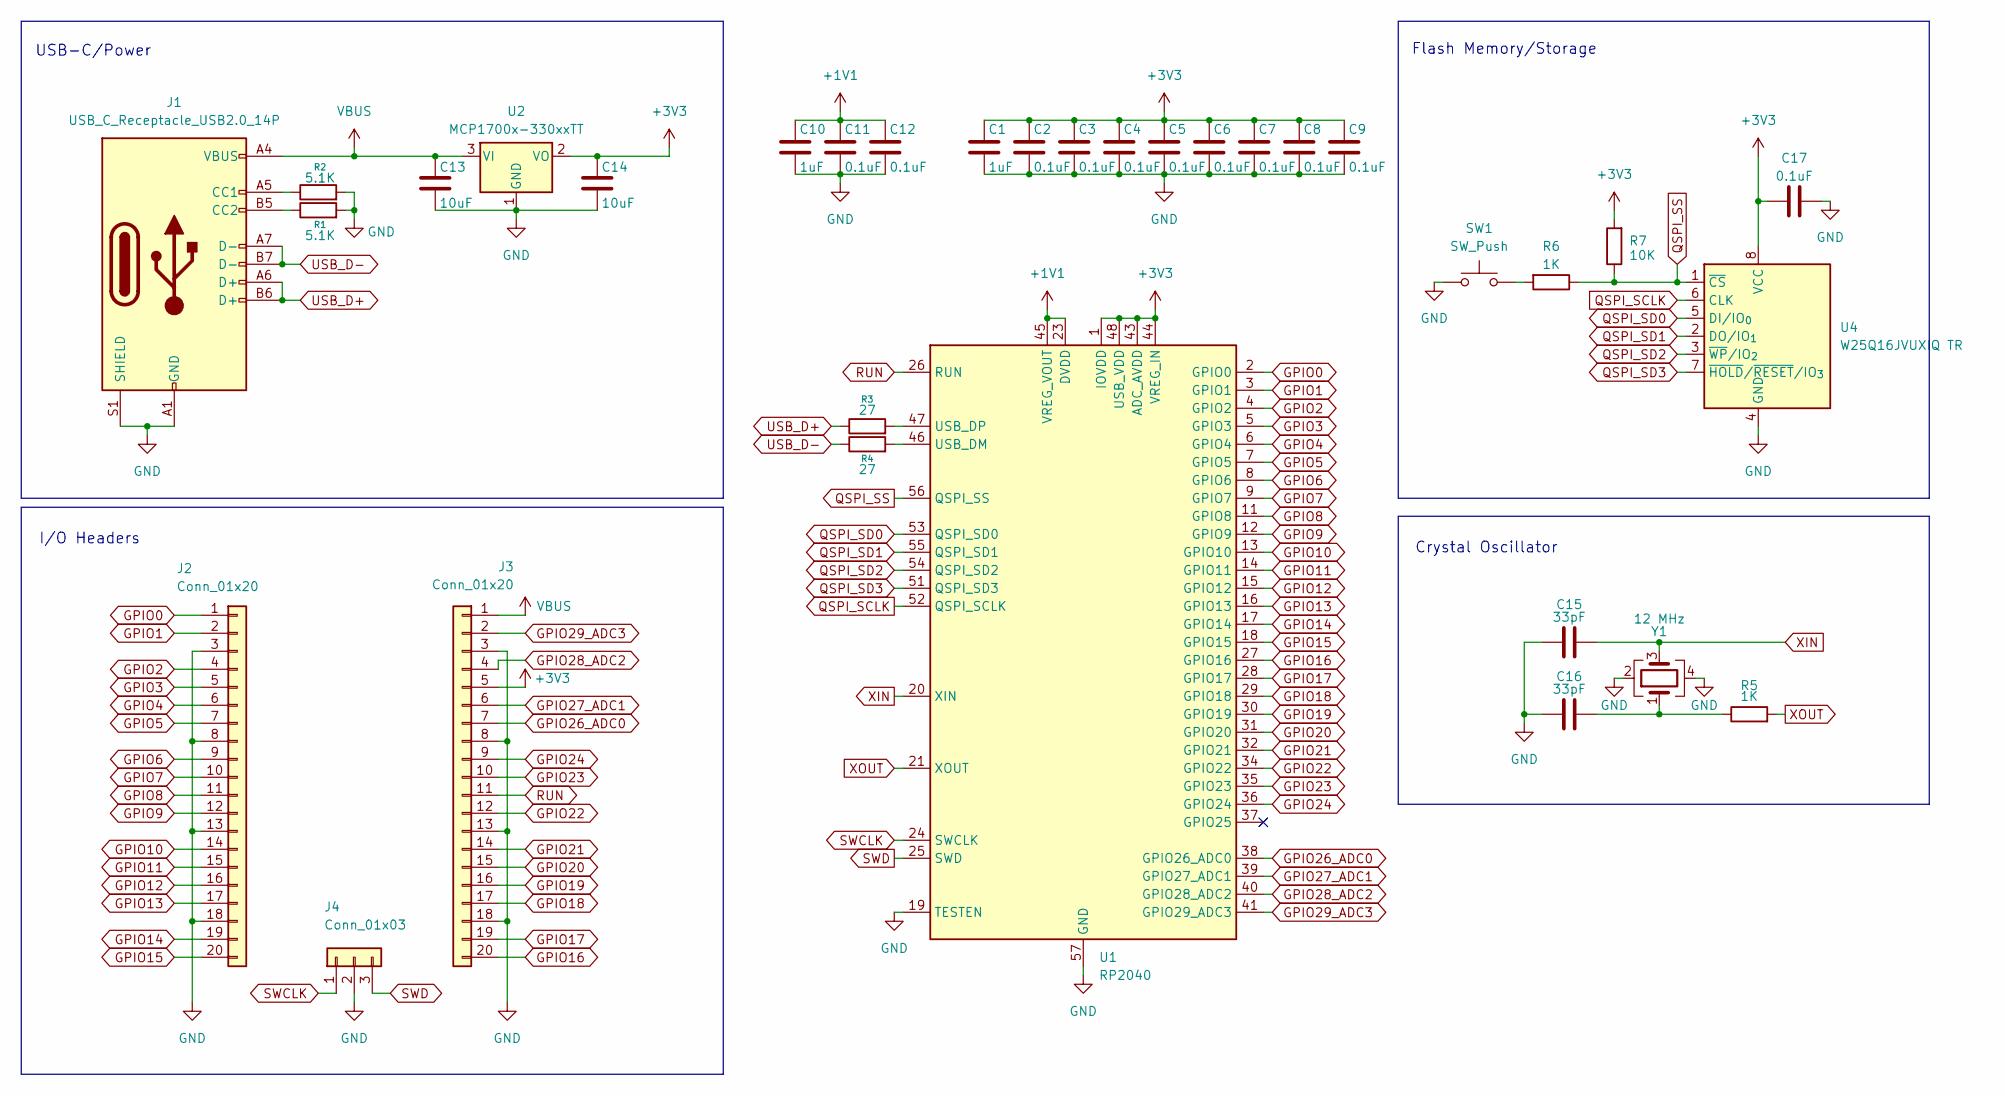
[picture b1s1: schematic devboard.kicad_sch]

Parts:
C1, C10: 1uF; C_0402_1005Metric
C2, C3, C4, C5, C6, C7, C8, C9, C11, C12, C17: 0.1uF; C_0402_1005Metric
C13, C14: 10uF; C_0603_1608Metric
C15, C16: 33pF; C_0402_1005Metric
J1: USB_C_Receptacle_USB2.0_14P; USB_C_Receptacle_HRO_TYPE-C-31-M-12
J2, J3: Conn_01x20; PinHeader_1x20_P2.54mm_Vertical
J4: Conn_01x03; PinHeader_1x03_P2.54mm_Vertical
R1, R2: 5.1K; R_0402_1005Metric
R3, R4: 27; R_0402_1005Metric
R5, R6: 1K; R_0402_1005Metric
R7: 10K; R_0402_1005Metric
SW1: SW_Push; SW_Push_SPST_NO_Alps_SKRK
U1: RP2040; QFN-56-1EP_7x7mm_P0.4mm_EP3.2x3.2mm
U2: MCP1700x-330xxTT; SOT-23
U4: W25Q16JVUXIQ TR; Winbond_USON-8-1EP_3x2mm_P0.5mm_EP0.2x1.6mm
Y1: 12 MHz; Crystal_SMD_3225-4Pin_3.2x2.5mm

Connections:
+1V1: C10.1, C11.1, C12.1, U1.23 (DVDD), U1.45 (VREG_VOUT), U1.50 (DVDD)
+3V3: C1.1, C2.1, C3.1, C4.1, C5.1, C6.1, C7.1, C8.1, C9.1, C14.1, C17.1, J3.5, R7.2, U1.1 (IOVDD), U1.10 (IOVDD), U1.22 (IOVDD), U1.33 (IOVDD), U1.42 (IOVDD), U1.43 (ADC_AVDD), U1.44 (VREG_IN), U1.48 (USB_VDD), U1.49 (IOVDD), U2.2 (VO), U4.8 (VCC)
GND: C1.2, C2.2, C3.2, C4.2, C5.2, C6.2, C7.2, C8.2, C9.2, C10.2, C11.2, C12.2, C13.2, C14.2, C15.1, C16.1, C17.2, J1.A1 (GND), J1.A12 (GND), J1.B1 (GND), J1.B12 (GND), J1.S1 (SHIELD), J2.3, J2.8, J2.13, J2.18, J3.3, J3.8, J3.13, J3.18, J4.2, R1.2, R2.2, SW1.1, U1.19 (TESTEN), U1.57 (GND), U2.1 (GND), U4.4 (GND), Y1.2, Y1.4
GPIO0: J2.1, U1.2 (GPIO0)
GPIO1: J2.2, U1.3 (GPIO1)
GPIO2: J2.4, U1.4 (GPIO2)
GPIO3: J2.5, U1.5 (GPIO3)
GPIO4: J2.6, U1.6 (GPIO4)
GPIO5: J2.7, U1.7 (GPIO5)
GPIO6: J2.9, U1.8 (GPIO6)
GPIO7: J2.10, U1.9 (GPIO7)
GPIO8: J2.11, U1.11 (GPIO8)
GPIO9: J2.12, U1.12 (GPIO9)
GPIO10: J2.14, U1.13 (GPIO10)
GPIO11: J2.15, U1.14 (GPIO11)
GPIO12: J2.16, U1.15 (GPIO12)
GPIO13: J2.17, U1.16 (GPIO13)
GPIO14: J2.19, U1.17 (GPIO14)
GPIO15: J2.20, U1.18 (GPIO15)
GPIO16: J3.20, U1.27 (GPIO16)
GPIO17: J3.19, U1.28 (GPIO17)
GPIO18: J3.17, U1.29 (GPIO18)
GPIO19: J3.16, U1.30 (GPIO19)
GPIO20: J3.15, U1.31 (GPIO20)
GPIO21: J3.14, U1.32 (GPIO21)
GPIO22: J3.12, U1.34 (GPIO22)
GPIO23: J3.10, U1.35 (GPIO23)
GPIO24: J3.9, U1.36 (GPIO24)
GPIO26_ADC0: J3.7, U1.38 (GPIO26_ADC0)
GPIO27_ADC1: J3.6, U1.39 (GPIO27_ADC1)
GPIO28_ADC2: J3.4, U1.40 (GPIO28_ADC2)
GPIO29_ADC3: J3.2, U1.41 (GPIO29_ADC3)
unnamed: C16.2, R5.1, Y1.1
unnamed: J1.A5 (CC1), R2.1
unnamed: J1.B5 (CC2), R1.1
unnamed: R6.2, SW1.2
unnamed: R4.2, U1.46 (USB_DM)
unnamed: R3.2, U1.47 (USB_DP)
QSPI_SCLK: U1.52 (QSPI_SCLK), U4.6 (CLK)
QSPI_SD0: U1.53 (QSPI_SD0), U4.5 (DI/IO_{0})
QSPI_SD1: U1.55 (QSPI_SD1), U4.2 (DO/IO_{1})
QSPI_SD2: U1.54 (QSPI_SD2), U4.3 (~WP/IO_{2})
QSPI_SD3: U1.51 (QSPI_SD3), U4.7 (~HOLD/~RESET/IO_{3})
QSPI_SS: R6.1, R7.1, U1.56 (QSPI_SS), U4.1 (~CS)
RUN: J3.11, U1.26 (RUN)
SWCLK: J4.1, U1.24 (SWCLK)
SWD: J4.3, U1.25 (SWD)
USB_D+: J1.A6 (D+), J1.B6 (D+), R3.1
USB_D-: J1.A7 (D-), J1.B7 (D-), R4.1
VBUS: C13.1, J1.A4 (VBUS), J1.A9 (VBUS), J1.B4 (VBUS), J1.B9 (VBUS), J3.1, U2.3 (VI)
XIN: C15.2, U1.20 (XIN), Y1.3
XOUT: R5.2, U1.21 (XOUT)

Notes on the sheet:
Flash Memory/Storage
I/O Headers
Crystal Oscillator
USB-C/Power

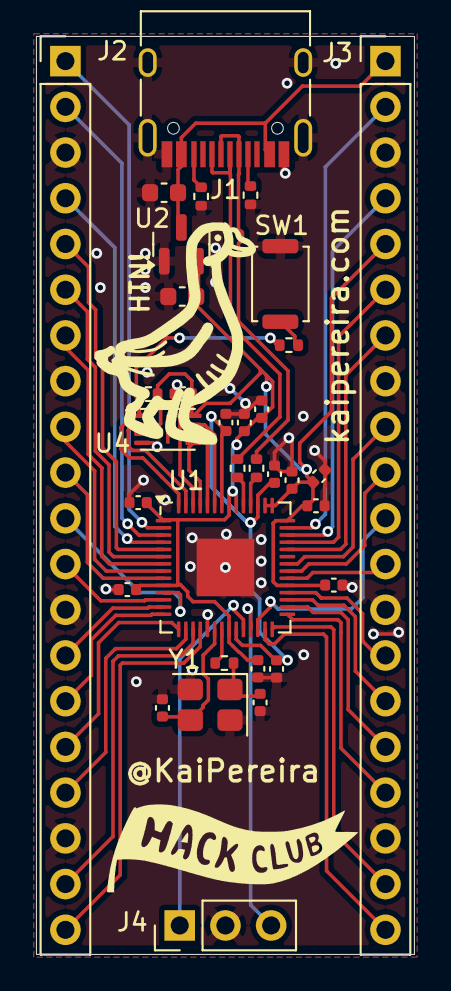
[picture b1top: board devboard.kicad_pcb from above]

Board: 2 copper layers, 21.0 x 51.0 mm, 33 parts (0 on the bottom side), 52 nets.

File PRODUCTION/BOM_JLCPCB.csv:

JLCPCB BOM Tool - BOM Matching,,,,,,,,,,,,,,,,,
BOM name：BOM-JLCPCB Assembly Order.xlsx,,,Download Time：2025-10-01 10:21:17,,,,"* Our matching results are updated in real-time, but stock and prices may change. 
If it's been over 24 hours, please re-match before placing your order.",,,,,,,,,,
PCB Assembled Qty：5,,,Est. Total Price：11.5620,,,,,,,,,,,,,,
Your BOM,,,,,Matched Parts,,,,,,,Order Information,,,,,
Top Designator,Bottom Designator,Comment,Footprint,JLCPCB Part #,Matches,Part # ,Manufacturer,Footprint,Description,Category,Warning,JLCPCB Part #,Product link,Lib Type,Qty,Source,Total Price ($)
"C1,C10",,1uF,C_0402_1005Metric,,Select by Customer,CL05A105KA5NQNC,Samsung Electro-Mechanics,0402,1uF 25V X5R ±10% 0402 Multilayer Ceramic Capacitors MLCC - SMD/SMT ROHS,Multilayer Ceramic Capacitors MLCC - SMD/SMT,,C52923,https://jlcpcb.com/partdetail/53938-CL05A105KA5NQNC/C52923,Basic,10,10 JLCPCB,0.029
"C8,C6,C5,C4,C2,C7,C11,C9,C12,C17,C3",,0.1uF,C_0402_1005Metric,,Select by Customer,CL05B104KO5NNNC,Samsung Electro-Mechanics,0402,100nF 16V X7R ±10% 0402 Multilayer Ceramic Capacitors MLCC - SMD/SMT ROHS,Multilayer Ceramic Capacitors MLCC - SMD/SMT,1.The comment (CL05B104KO5NNNC) of this part does not match the one (0.1uF) provided in your BOM. Please confirm;,C1525,https://jlcpcb.com/partdetail/1877-CL05B104KO5NNNC/C1525,Basic,55,55 JLCPCB,0.0605
"C13,C14",,10uF,C_0603_1608Metric,,Select by System,CL10A106KP8NNNC,Samsung Electro-Mechanics,0603,10V 10uF X5R ±10% 0603 Multilayer Ceramic Capacitors MLCC - SMD/SMT ROHS,Multilayer Ceramic Capacitors MLCC - SMD/SMT,,C19702,https://jlcpcb.com/partdetail/20411-CL10A106KP8NNNC/C19702,Basic,10,10 JLCPCB,0.056
"C16,C15",,33pF,C_0402_1005Metric,,Select by Customer,0402CG330J500NT,FH (Guangdong Fenghua Advanced Tech),0402,33pF 50V C0G ±5% 0402 Multilayer Ceramic Capacitors MLCC - SMD/SMT ROHS,Multilayer Ceramic Capacitors MLCC - SMD/SMT,,C1562,https://jlcpcb.com/partdetail/1914-0402CG330J500NT/C1562,Basic,10,10 JLCPCB,0.01
J1,,USB_C_Receptacle_USB2.0_14P,USB_C_Receptacle_HRO_TYPE-C-31-M-12,,Select by Customer,TYPE-C-31-M-12,Korean Hroparts Elec,SMD,1 16P 5A Female Type-C SMD USB Connectors ROHS,USB Connectors,,C165948,https://jlcpcb.com/partdetail/Korean_HropartsElec-TYPE_C_31_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,Extended,5,5 JLCPCB,0.8445
"J3,J2",,Conn_01x20,PinHeader_1x20_P2.54mm_Vertical,,Select by Customer,2.54-1*20P直针,BOOMELE(Boom Precision Elec),"插件,P=2.54mm","-40℃~+105℃ 1 1x20P 2.54mm 20P 3A Black Brass Pin Header Through Hole Plugin,P=2.54mm Pin Headers ROHS",Pin Headers,,C50981,https://jlcpcb.com/partdetail/51993-2_54_1_20P/C50981,Extended,0,0 JLCPCB,0
J4,,Conn_01x03,PinHeader_1x03_P2.54mm_Vertical,,Select by Customer,1.27-1*3P针,BOOMELE(Boom Precision Elec),"插件,P=1.27mm","-55℃~+105℃ 1 1.27mm 1mm 1x3P 2.3mm 3A 3P 3mm Black Brass Pin Header Through Hole Plugin,P=1.27mm Pin Headers ROHS",Pin Headers,,C24980,https://jlcpcb.com/partdetail/25717-1_27_1_3P/C24980,Extended,0,0 JLCPCB,0
"R2,R1",,5.1K,R_0402_1005Metric,,Select by Customer,0402WGF5101TCE,UNI-ROYAL(Uniroyal Elec),0402,-55℃~+155℃ 5.1kΩ 50V 62.5mW Thick Film Resistor ±1% ±100ppm/℃ 0402 Chip Resistor - Surface Mount ROHS,Chip Resistor - Surface Mount,,C25905,https://jlcpcb.com/partdetail/26648-0402WGF5101TCE/C25905,Basic,10,10 JLCPCB,0.005
"R3,R4",,27,R_0402_1005Metric,,Select by Customer,0402WGF270JTCE,UNI-ROYAL(Uniroyal Elec),0402,-55℃~+155℃ 27Ω 50V 62.5mW Thick Film Resistor ±1% ±100ppm/℃ 0402 Chip Resistor - Surface Mount ROHS,Chip Resistor - Surface Mount,1.The comment (0402WGF270JTCE) of this part does not match the one (27) provided in your BOM. Please confirm;,C25100,https://jlcpcb.com/partdetail/25843-0402WGF270JTCE/C25100,Extended,22,22 JLCPCB,0.011
"R6,R5",,1K,R_0402_1005Metric,,Select by Customer,0402WGF1001TCE,UNI-ROYAL(Uniroyal Elec),0402,-55℃~+155℃ 1kΩ 50V 62.5mW Thick Film Resistor ±1% ±100ppm/℃ 0402 Chip Resistor - Surface Mount ROHS,Chip Resistor - Surface Mount,1.The comment (0402WGF1001TCE) of this part does not match the one (1K) provided in your BOM. Please confirm;,C11702,https://jlcpcb.com/partdetail/12256-0402WGF1001TCE/C11702,Basic,10,10 JLCPCB,0.005
R7,,10K,R_0402_1005Metric,,Select by Customer,0402WGF1002TCE,UNI-ROYAL(Uniroyal Elec),0402,-55℃~+155℃ 10kΩ 50V 62.5mW Thick Film Resistor ±1% ±100ppm/℃ 0402 Chip Resistor - Surface Mount ROHS,Chip Resistor - Surface Mount,1.The comment (0402WGF1002TCE) of this part does not match the one (10K) provided in your BOM. Please confirm;,C25744,https://jlcpcb.com/partdetail/26487-0402WGF1002TCE/C25744,Basic,5,5 JLCPCB,0.0025
SW1,,SW_Push,SW_Push_SPST_NO_Alps_SKRK,,Select by Customer,TS-1088-AR02016,XUNPU,"SMD,4x3mm","-30℃~+80℃ 1.6N 100,000 Cycles 12V 2mm 3mm 4mm 50mA Black Round Button SMD(SMT) Tab SPST Surface Mount,Vertical Without Bracket SMD,4x3mm Tactile Switches ROHS",Tactile Switches,,C720477,https://jlcpcb.com/partdetail/XUNPU-TS_1088AR02016/C720477,Basic,5,5 JLCPCB,0.2115
U1,,RP2040,QFN-56-1EP_7x7mm_P0.4mm_EP3.2x3.2mm,,Select by Customer,RP2040,Raspberry Pi,LQFN-56(7x7),12bit 133MHz 30 LQFN-56(7x7) Microcontrollers (MCU/MPU/SOC) ROHS,Microcontrollers (MCU/MPU/SOC),,C2040,https://jlcpcb.com/partdetail/RaspberryPi-RP2040/C2040,Extended,5,5 JLCPCB,5.5275
U2,,MCP1700x-330xxTT,SOT-23,,Select by Customer,MCP1700T-3302E/TT,Microchip Tech,SOT-23,"-40℃~+125℃@(Tj) 1 1.6uA 178mV@(250mA) 250mA 3.3V 44dB@(100Hz) 6V Fixed Over Temperature Protection Positive SOT-23 Voltage Regulators - Linear, Low Drop Out (LDO) Regulators ROHS","Voltage Regulators - Linear, Low Drop Out (LDO) Regulators",,C39051,https://jlcpcb.com/partdetail/MicrochipTech-MCP1700T_3302ETT/C39051,Extended,5,5 JLCPCB,1.717
U4,,W25Q16JVUXIQTR,Winbond_USON-8-1EP_3x2mm_P0.5mm_EP0.2x1.6mm,,Select by Customer,W25Q16JVUXIQ,Winbond Elec,USON-8-EP(2x3),"100,000 Cycles 133MHz 16Mbit 2.7V~3.6V 20 Years 3ms SPI USON-8-EP(2x3) NOR FLASH ROHS",NOR FLASH,1.The comment (W25Q16JVUXIQ) of this part does not match the one (W25Q16JVUXIQTR) provided in your BOM. Please confirm;,C2843335,https://jlcpcb.com/partdetail/WinbondElec-W25Q16JVUXIQ/C2843335,Extended,5,5 JLCPCB,2.76
Y1,,12MHz,Crystal_SMD_3225-4Pin_3.2x2.5mm,,Select by Customer,X322512MSB4SI,YXC Crystal Oscillators,SMD3225-4P,-40℃~+85℃ 12MHz 20pF Crystal Oscillator ±10ppm ±20ppm SMD3225-4P Crystals ROHS,Crystals,,C9002,https://jlcpcb.com/partdetail/YXC_CrystalOscillators-X322512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,Basic,5,5 JLCPCB,0.3225

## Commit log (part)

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2025-09-25 init
2025-09-25 fixing hierarchy
2025-09-25 actually fixing hierarchy this time, whoops
2025-09-25 working on tutorial
2025-09-25 working on power stuff
2025-09-25 finished power decoupling
2025-09-25 working on USB
2025-09-25 fixed images
2025-09-25 merge
2025-09-25 finished USB-C wiring
2025-09-25 fix images
2025-09-25 fixing the journal and USB on MCU
2025-09-25 fixing images
2025-09-26 added crystal
2025-09-26 Fixed images, I love VIM
2025-09-26 talking about SPI, started quad SPI
2025-09-26 working on QSPI
2025-09-26 added flash memory
2025-09-28 finished flash memory
2025-09-28 working on breakout out GPIO's
2025-09-28 forgot to save schematic
2025-09-28 almost done pin headers
2025-09-28 finished adding in the I/O headers
2025-09-28 organizing schematic
2025-09-28 working on footprints and journalled organizaton
2025-09-28 update the footprint journal
2025-09-28 starting PCB
2025-09-28 working on changing headers to be correct
2025-09-28 Fixed a bunch of images
2025-09-29 finishing the schematic refined
2025-09-29 assigned new footpritns and updating journal
2025-09-29 fixed all images finally with new schematic
2025-09-29 mounting holes and outline
2025-09-29 removing mounting holes, not enough space
2025-09-29 aligned pin headers
2025-09-29 aligning USB-C and SoC
2025-09-29 fixed LDO and flash memory, did lots of layout stuff
2025-09-29 added all the decoupling capacitors
2025-09-29 starting to route
2025-09-29 routing differential pairs
2025-09-29 a bunch more routing
2025-09-29 more routing
2025-09-30 finished routing signals
2025-09-30 updated journal
2025-09-30 some ground fill stuff
2025-09-30 all the GND's and thermal relief stuff
2025-09-30 removed all ratlines
2025-09-30 fixing DRC
2025-09-30 fixed all thermal relief errors
2025-09-30 finished the main PCBH
2025-09-30 fixed journal
2025-09-30 organized silkscreen
2025-09-30 working on custom silkscreen
2025-09-30 added silkscreen
2025-09-30 added production files
2025-09-30 fixed production files, lots of journal stuff too
2025-09-30 updating the production files
2025-09-30 working on BOM
2025-09-30 update BOM another time, this time it should be good
2025-09-30 board checkout
2025-09-30 finished the tutorial rough draft
2025-09-30 updated the journal
2025-09-30 adding in the initial images for the board
2025-09-30 Testing if url's work in markdown
2025-09-30 Maybe this works?
2025-09-30 Reverting... That didn't work...
2025-09-30 adding finishing touches
2025-09-30 added readme
2025-09-30 Basic readme
2025-09-30 more final touches on the tutorial
2025-10-01 fixed BOM
2025-10-01 proofreading my tutorial
2025-10-01 fixed clock label direction for flash lol, more proofreading
2025-10-01 more proofreading
2025-10-01 finished proofreading
2025-10-02 updated production files to fix some silkscreen lol
2025-10-03 adding pcb3d
2025-10-03 working on renders
2025-10-03 ready to render!
2025-10-03 finished rendering
2025-10-03 working on 2nd render
2025-10-03 starting to render
2025-10-03 added new render
2025-10-26 added the CSV file so I can look at it while soldering :D
2025-10-26 added your workspace to the devboard tutorial
2025-10-26 removed random md file that appeared??
2025-10-26 described howhow to solder components onto the actual board!
2025-10-26 fixing an image
2025-11-15 Oops, fixing the link!
2025-11-15 Fixing the link to the tutorial in the readme again!
2025-11-22 Changing readme to journal!
